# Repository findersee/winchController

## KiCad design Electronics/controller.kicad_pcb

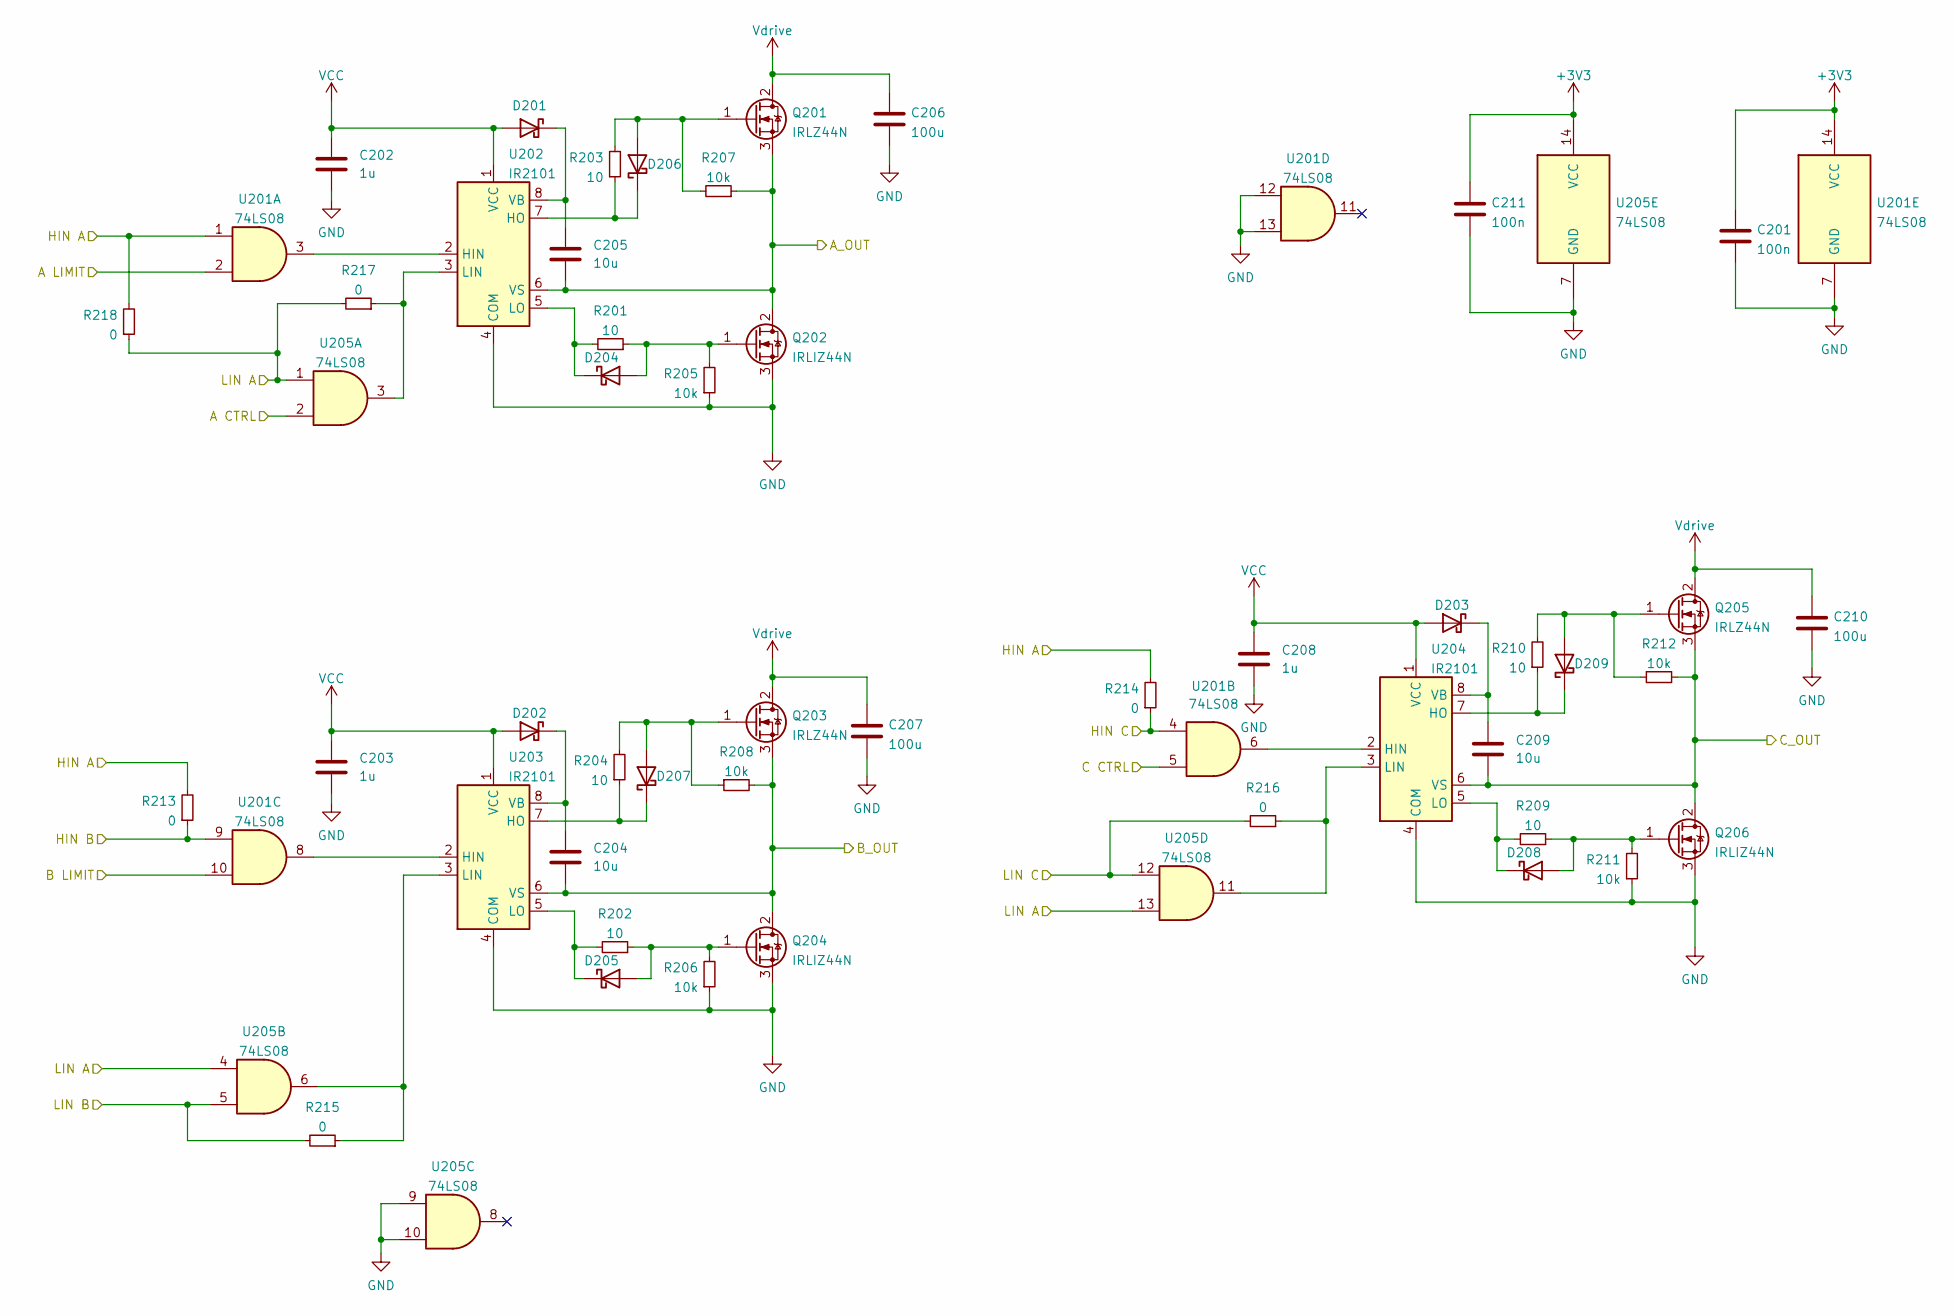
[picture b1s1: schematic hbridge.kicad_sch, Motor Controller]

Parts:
C201, C211: 100n; C_0603_1608Metric_Pad1.08x0.95mm_HandSolder
C202, C203, C208: 1u; C_0603_1608Metric_Pad1.08x0.95mm_HandSolder
C204, C205, C209: 10u; R_0805_2012Metric_Pad1.20x1.40mm_HandSolder
C206, C207, C210: 100u; CP_Radial_D12.5mm_P3.5-5.0mm
D201, D202, D203, D204, D205, D206, D207, D208, D209: 1N5819; D_SOD-123
Q201, Q203, Q205: IRLZ44N; TO-220-3_Vertical
Q202, Q204, Q206: IRLIZ44N; TO-220F-3_Vertical
R201, R202, R203, R204, R209, R210: 10; R_0805_2012Metric_Pad1.20x1.40mm_HandSolder
R205, R206, R207, R208, R211, R212: 10k; R_0805_2012Metric_Pad1.20x1.40mm_HandSolder
R213, R214, R215, R216, R217, R218: 0; R_0603_1608Metric_Pad0.98x0.95mm_HandSolder
U201, U205: 74LS08; SO-14_3.9x8.65mm_P1.27mm
U202, U203, U204: IR2101; SO-8_3.9x4.9mm_P1.27mm

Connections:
+3V3: C201.1, C211.1, U201.14 (VCC), U205.14 (VCC); also elsewhere on the board
/Connectors/Limit 1: U201.2; also elsewhere on the board
/Connectors/Limit 2: U201.10; also elsewhere on the board
/Connectors/MOTOR C: C209.1, Q205.3 (S), Q206.2 (D), R212.2, U204.6 (VS); also elsewhere on the board
/Connectors/MOTOR NEG: C204.1, Q203.3 (S), Q204.2 (D), R208.2, U203.6 (VS); also elsewhere on the board
/Connectors/MOTOR POS: C205.1, Q201.3 (S), Q202.2 (D), R207.1, U202.6 (VS); also elsewhere on the board
/Hbridge/A CTRL: U205.2; also elsewhere on the board
/Hbridge/C CTRL: U201.5; also elsewhere on the board
/Hbridge/HIN A: R213.2, R214.2, R218.2, U201.1; also elsewhere on the board
/Hbridge/HIN B: R213.1, U201.9; also elsewhere on the board
/Hbridge/HIN C: R214.1, U201.4; also elsewhere on the board
/Hbridge/LIN A: R217.2, R218.1, U205.1, U205.4, U205.13; also elsewhere on the board
/Hbridge/LIN B: R215.2, U205.5; also elsewhere on the board
/Hbridge/LIN C: R216.2, U205.12; also elsewhere on the board
GND: C201.2, C202.1, C203.1, C206.2, C207.2, C208.1, C210.2, C211.2, Q202.3 (S), Q204.3 (S), Q206.3 (S), R205.1, R206.1, R211.1, U201.7 (GND), U201.12, U201.13, U202.4 (COM), U203.4 (COM), U204.4 (COM), U205.7 (GND), U205.9, U205.10; also elsewhere on the board
unnamed: C204.2, D202.1 (K), U203.8 (VB)
unnamed: C205.2, D201.1 (K), U202.8 (VB)
unnamed: C209.2, D203.1 (K), U204.8 (VB)
unnamed: D204.1 (K), R201.2, U202.5 (LO)
unnamed: D204.2 (A), Q202.1 (G), R201.1, R205.2
unnamed: D205.1 (K), R202.2, U203.5 (LO)
unnamed: D205.2 (A), Q204.1 (G), R202.1, R206.2
unnamed: D206.1 (K), R203.1, U202.7 (HO)
unnamed: D206.2 (A), Q201.1 (G), R203.2, R207.2
unnamed: D207.1 (K), R204.1, U203.7 (HO)
unnamed: D207.2 (A), Q203.1 (G), R204.2, R208.1
unnamed: D208.1 (K), R209.2, U204.5 (LO)
unnamed: D208.2 (A), Q206.1 (G), R209.1, R211.2
unnamed: D209.1 (K), R210.1, U204.7 (HO)
unnamed: D209.2 (A), Q205.1 (G), R210.2, R212.1
unnamed: R215.1, U203.3 (LIN), U205.6
unnamed: R216.1, U204.3 (LIN), U205.11
unnamed: R217.1, U202.3 (LIN), U205.3
unnamed: U201.3, U202.2 (HIN)
unnamed: U201.6, U204.2 (HIN)
unnamed: U201.8, U203.2 (HIN)
VCC: C202.2, C203.2, C208.2, D201.2 (A), D202.2 (A), D203.2 (A), U202.1 (VCC), U203.1 (VCC), U204.1 (VCC); also elsewhere on the board
Vdrive: C206.1, C207.1, C210.1, Q201.2 (D), Q203.2 (D), Q205.2 (D); also elsewhere on the board

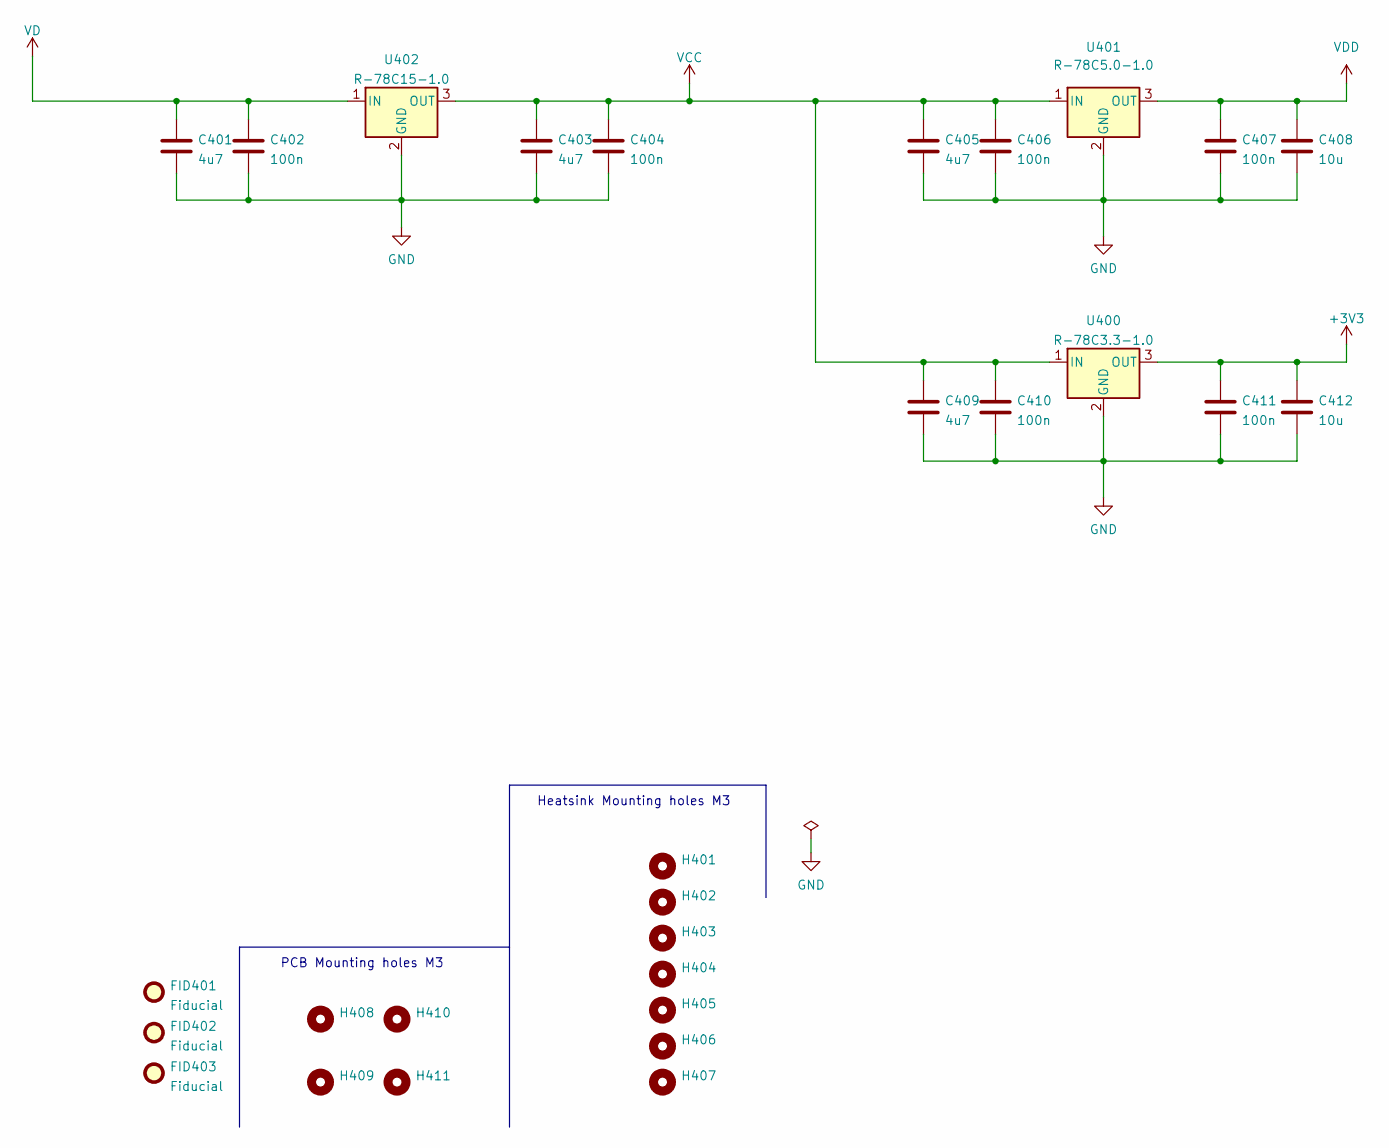
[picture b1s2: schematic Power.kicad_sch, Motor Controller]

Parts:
C401, C403, C405, C409: 4u7; R_0805_2012Metric_Pad1.20x1.40mm_HandSolder
C402, C404, C406, C407, C410, C411: 100n; C_0603_1608Metric_Pad1.08x0.95mm_HandSolder
C408, C412: 10u; R_0805_2012Metric_Pad1.20x1.40mm_HandSolder
FID401, FID402, FID403: Fiducial; Fiducial_1.5mm_Mask3mm
H401, H402, H403, H404, H405, H406, H407, H408, H409, H410, H411: MountingHole; MountingHole_3.2mm_M3_DIN965
U400: R-78C3.3-1.0; Converter_DCDC_RECOM_R-78E-0.5_THT
U401: R-78C5.0-1.0; Converter_DCDC_RECOM_R-78E-0.5_THT
U402: R-78C15-1.0; Converter_DCDC_RECOM_R-78E-0.5_THT

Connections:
+3V3: C411.1, C412.1, U400.3 (OUT); also elsewhere on the board
GND: C401.2, C402.2, C403.2, C404.2, C405.2, C406.2, C407.2, C408.2, C409.2, C410.2, C411.2, C412.2, U400.2 (GND), U401.2 (GND), U402.2 (GND); also elsewhere on the board
VCC: C403.1, C404.1, C405.1, C406.1, C409.1, C410.1, U400.1 (IN), U401.1 (IN), U402.3 (OUT); also elsewhere on the board
VD: C401.1, C402.1, U402.1 (IN); also elsewhere on the board
VDD: C407.1, C408.1, U401.3 (OUT); also elsewhere on the board

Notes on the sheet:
PCB Mounting holes M3
Heatsink Mounting holes M3

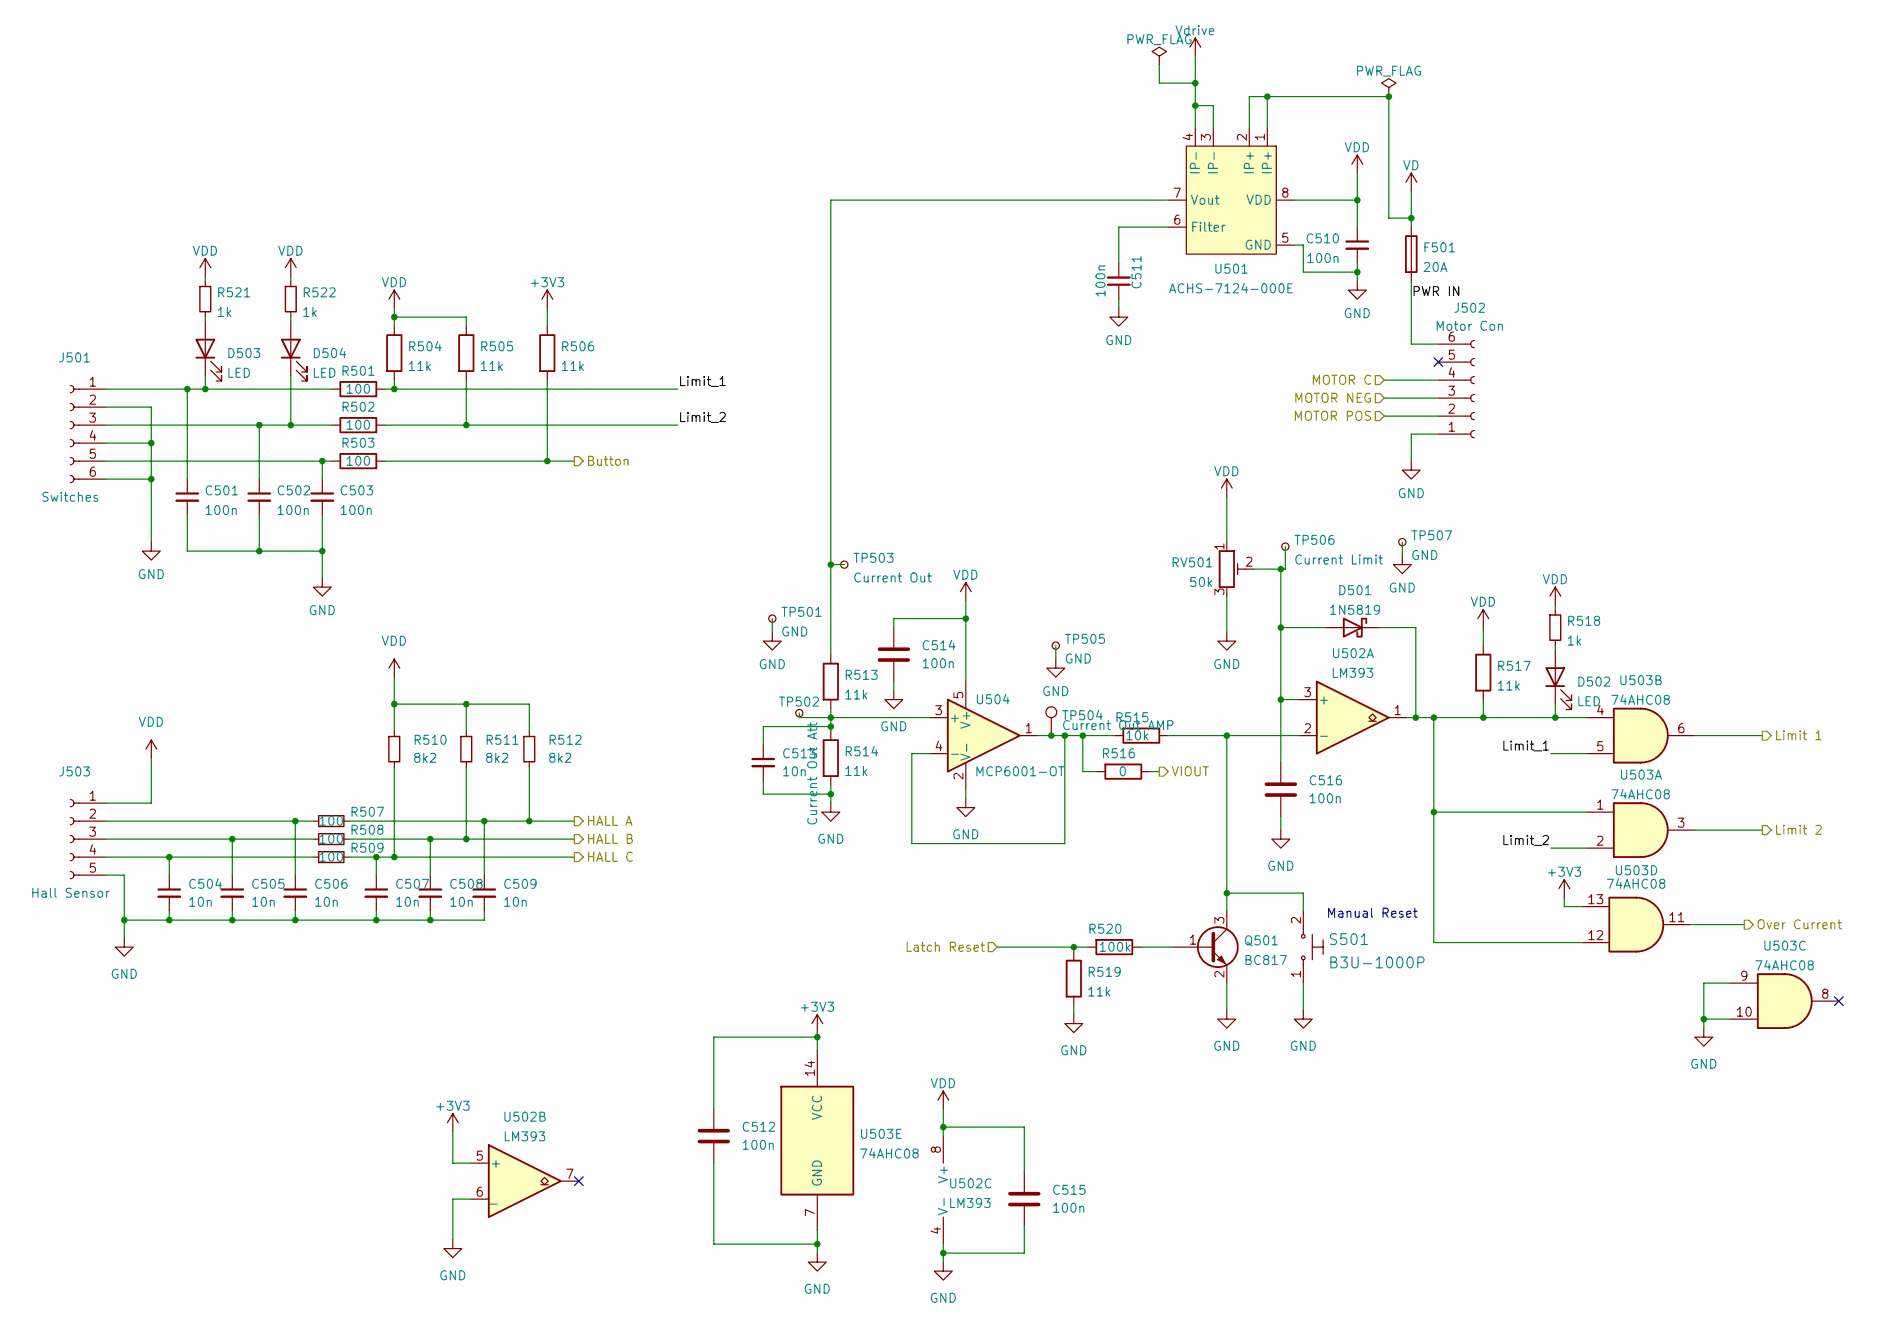
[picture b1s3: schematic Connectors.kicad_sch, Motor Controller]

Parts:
C501, C502, C503, C510, C511, C512, C514, C515, C516: 100n; C_0603_1608Metric_Pad1.08x0.95mm_HandSolder
C504, C505, C506, C507, C508, C509, C513: 10n; C_0603_1608Metric_Pad1.08x0.95mm_HandSolder
D501: 1N5819; D_SOD-123
D502, D503, D504: LED; LED_1206_3216Metric_Pad1.42x1.75mm_HandSolder
F501: 20A; 3550-2_KEYS
J501: Switches; TerminalBlock_bornier-6_P5.08mm
J502: Motor Con; TerminalBlock_bornier-6_P5.08mm
J503: Hall Sensor; PinHeader_1x05_P2.54mm_Vertical
Q501: BC817; SOT-23
R501, R502, R503, R507, R508, R509: 100; R_0603_1608Metric_Pad0.98x0.95mm_HandSolder
R504, R505, R506, R513, R514, R517, R519: 11k; R_0603_1608Metric_Pad0.98x0.95mm_HandSolder
R510, R511, R512: 8k2; R_0603_1608Metric_Pad0.98x0.95mm_HandSolder
R515: 10k; R_0603_1608Metric_Pad0.98x0.95mm_HandSolder
R516: 0; R_0603_1608Metric_Pad0.98x0.95mm_HandSolder
R518, R521, R522: 1k; LED_0603_1608Metric_Pad1.05x0.95mm_HandSolder
R520: 100k; R_0603_1608Metric_Pad0.98x0.95mm_HandSolder
RV501: 50k; Potentiometer_Vishay_TS53YJ_Vertical
S501: B3U-1000P; Switch_Tactile_SMD_B3U-1000P; MPN B3U-1000P; Digi-Key_PN SW1020CT-ND
TP501, TP505, TP507: GND; TestPoint_Pad_1.5x1.5mm
TP502: Current Out Att; TestPoint_Pad_D1.0mm
TP503: Current Out; TestPoint_Pad_D1.0mm
TP504: Current Out AMP; TestPoint_Pad_D1.0mm
TP506: Current Limit; TestPoint_Pad_D1.0mm
U501: ‎ACHS-7124-000E‎; SO-8_3.9x4.9mm_P1.27mm
U502: LM393; SO-8_3.9x4.9mm_P1.27mm
U503: 74AHC08; SSOP-14_5.3x6.2mm_P0.65mm
U504: MCP6001-OT; SOT-23-5

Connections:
+3V3: C512.2, R506.1, U502.5 (+), U503.13, U503.14 (VCC); also elsewhere on the board
/Connectors/Button: R503.2, R506.2; also elsewhere on the board
/Connectors/HALL A: C509.1, R507.2, R512.2; also elsewhere on the board
/Connectors/HALL B: C508.1, R508.2, R511.2; also elsewhere on the board
/Connectors/HALL C: C507.1, R509.2, R510.2; also elsewhere on the board
/Connectors/Latch Reset: R519.1, R520.2; also elsewhere on the board
/Connectors/Limit 1: U503.6; also elsewhere on the board
/Connectors/Limit 2: U503.3; also elsewhere on the board
/Connectors/Limit_1: R501.2, R504.2, U503.5
/Connectors/Limit_2: R502.2, R505.2, U503.2
/Connectors/MOTOR C: J502.4; also elsewhere on the board
/Connectors/MOTOR NEG: J502.3; also elsewhere on the board
/Connectors/MOTOR POS: J502.2; also elsewhere on the board
/Connectors/Over Current: U503.11; also elsewhere on the board
/Connectors/PWR IN: F501.2, J502.6
/Connectors/VIOUT: R516.1; also elsewhere on the board
GND: C501.2, C502.2, C503.2, C504.2, C505.2, C506.2, C507.2, C508.2, C509.2, C510.2, C511.1, C512.1, C513.2, C514.1, C515.1, C516.1, J501.2, J501.4, J501.6, J502.1, J503.5, Q501.2 (E), R514.2, R519.2, RV501.3, S501.1, TP501.1, TP505.1, TP507.1, U501.5 (GND), U502.4 (V-), U502.6 (_), U503.7 (GND), U503.9, U503.10, U504.2 (V-); also elsewhere on the board
unnamed: C501.1, D503.1 (K), J501.1, R501.1
unnamed: C502.1, D504.1 (K), J501.3, R502.1
unnamed: C503.1, J501.5, R503.1
unnamed: C504.1, J503.4, R509.1
unnamed: C505.1, J503.3, R508.1
unnamed: C506.1, J503.2, R507.1
unnamed: C511.2, U501.6 (Filter)
unnamed: C513.1, R513.2, R514.1, TP502.1, U504.3 (+)
unnamed: C516.2, D501.2 (A), RV501.2, TP506.1, U502.3 (+)
unnamed: D501.1 (K), D502.1 (K), R517.2, U502.1, U503.1, U503.4, U503.12
unnamed: D502.2 (A), R518.2
unnamed: D503.2 (A), R521.2
unnamed: D504.2 (A), R522.2
unnamed: Q501.1 (B), R520.1
unnamed: Q501.3 (C), R515.1, S501.2, U502.2 (-)
unnamed: R513.1, TP503.1, U501.7 (Vout)
unnamed: R515.2, R516.2, TP504.1, U504.1, U504.4 (-)
VD: F501.1, U501.1 (IP+), U501.2 (IP+); also elsewhere on the board
VDD: C510.1, C514.2, C515.2, J503.1, R504.1, R505.1, R510.1, R511.1, R512.1, R517.1, R518.1, R521.1, R522.1, RV501.1, U501.8 (VDD), U502.8 (V+), U504.5 (V+); also elsewhere on the board
Vdrive: U501.3 (IP-), U501.4 (IP-); also elsewhere on the board

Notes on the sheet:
Manual Reset

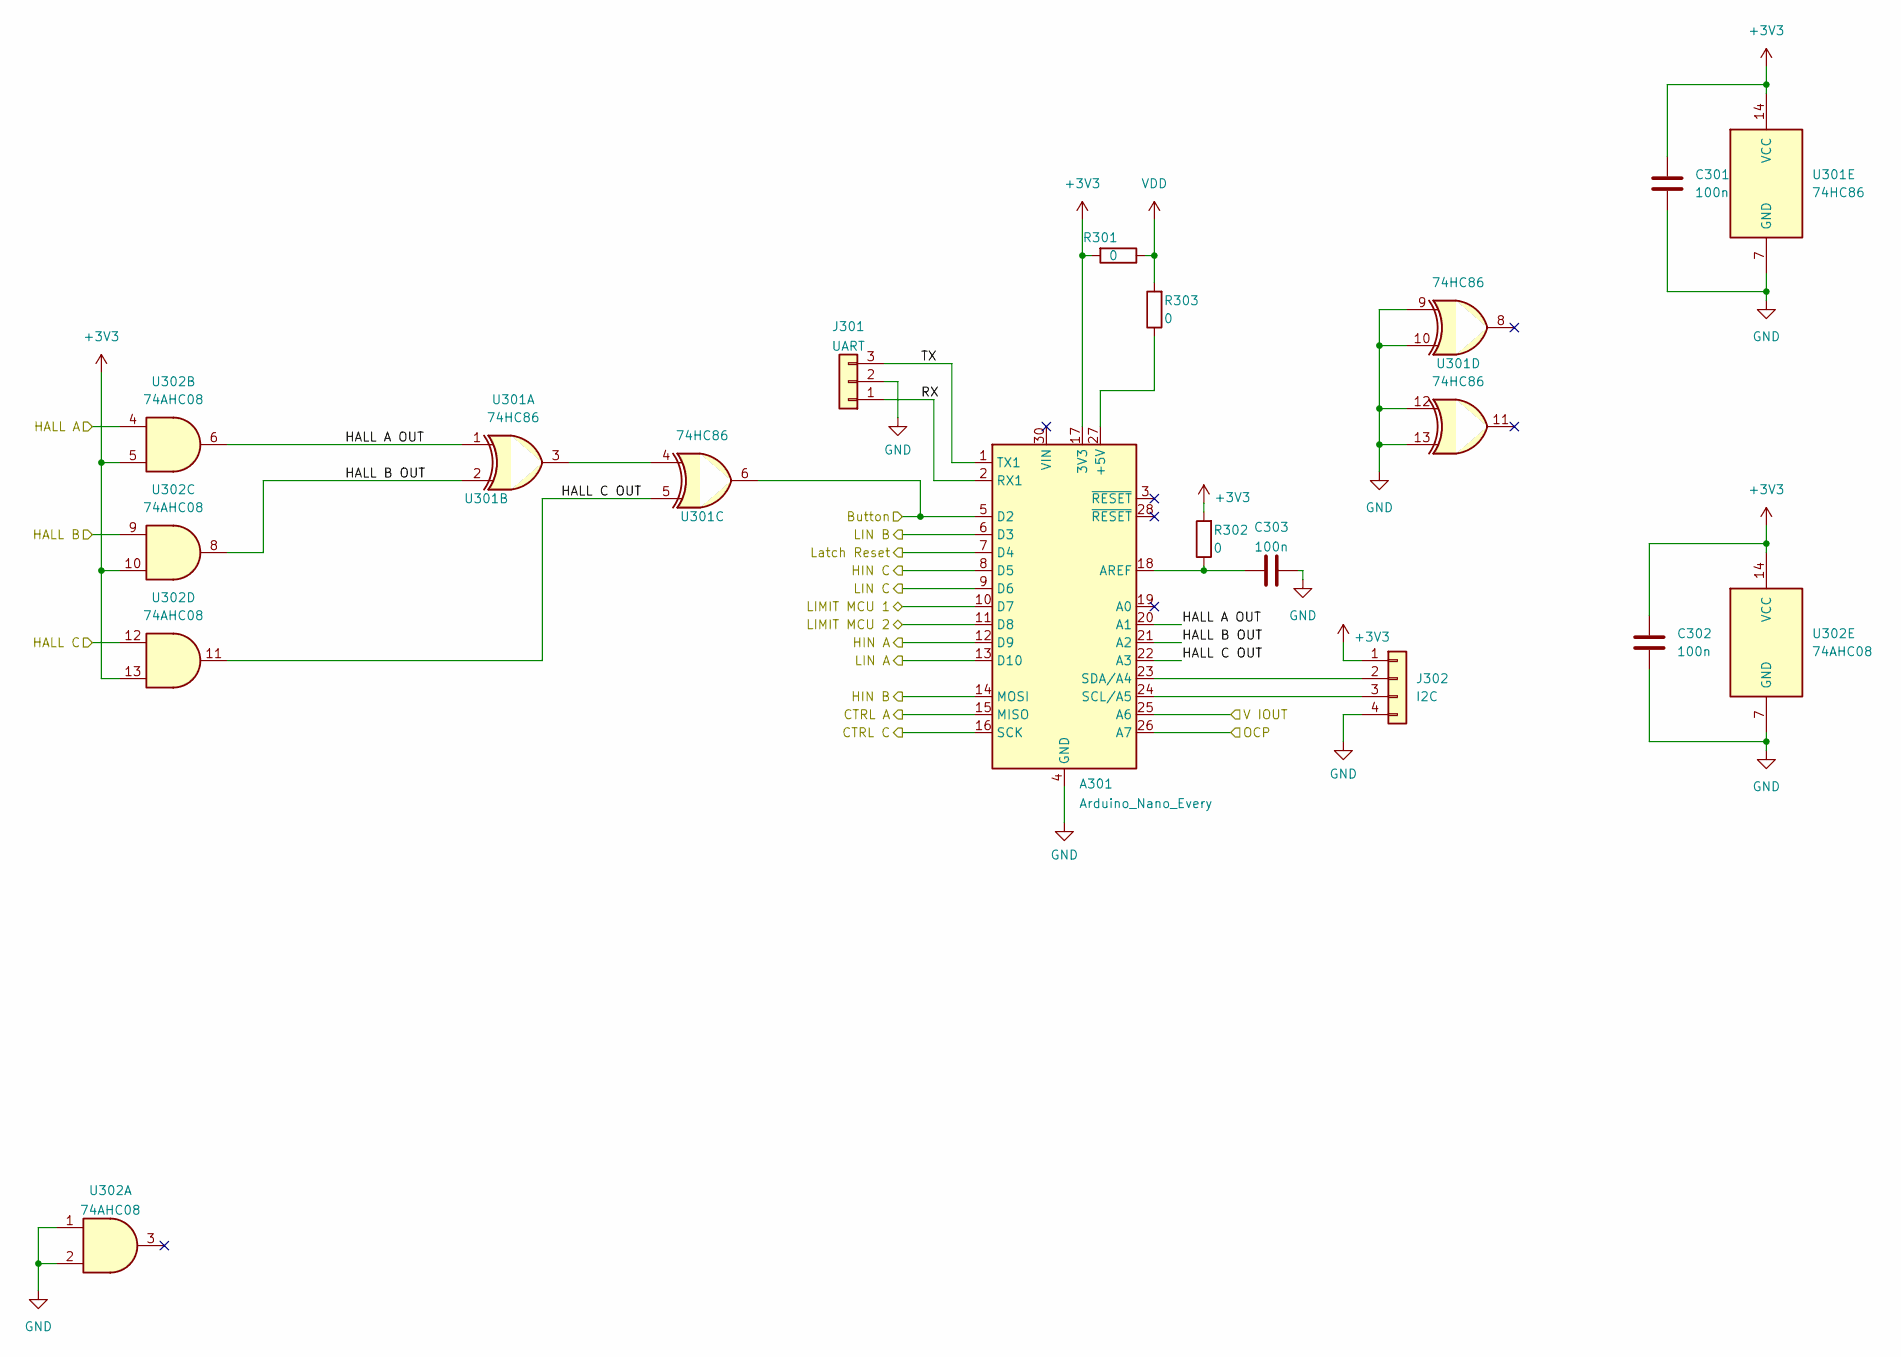
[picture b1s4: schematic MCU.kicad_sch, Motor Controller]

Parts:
A301: Arduino_Nano_Every; Arduino_Nano
C301, C302, C303: 100n; C_0603_1608Metric_Pad1.08x0.95mm_HandSolder
J301: UART; PinHeader_1x03_P2.54mm_Vertical
J302: I2C; PinHeader_1x04_P2.54mm_Vertical
R301, R302, R303: 0; R_0603_1608Metric_Pad0.98x0.95mm_HandSolder
U301: 74HC86; SO-14_3.9x8.65mm_P1.27mm
U302: 74AHC08; SSOP-14_5.3x6.2mm_P0.65mm

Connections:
+3V3: A301.17 (3V3), C301.2, C302.2, J302.1, R301.2, R302.2, U301.14 (VCC), U302.5, U302.10, U302.13, U302.14 (VCC); also elsewhere on the board
/Connectors/Button: A301.5 (D2), U301.6; also elsewhere on the board
/Connectors/HALL A: U302.4; also elsewhere on the board
/Connectors/HALL B: U302.9; also elsewhere on the board
/Connectors/HALL C: U302.12; also elsewhere on the board
/Connectors/Latch Reset: A301.7 (D4); also elsewhere on the board
/Connectors/Limit 1: A301.10 (D7); also elsewhere on the board
/Connectors/Limit 2: A301.11 (D8); also elsewhere on the board
/Connectors/Over Current: A301.26 (A7); also elsewhere on the board
/Connectors/VIOUT: A301.25 (A6); also elsewhere on the board
/Hbridge/A CTRL: A301.15 (MISO); also elsewhere on the board
/Hbridge/C CTRL: A301.16 (SCK); also elsewhere on the board
/Hbridge/HIN A: A301.12 (D9); also elsewhere on the board
/Hbridge/HIN B: A301.14 (MOSI); also elsewhere on the board
/Hbridge/HIN C: A301.8 (D5); also elsewhere on the board
/Hbridge/LIN A: A301.13 (D10); also elsewhere on the board
/Hbridge/LIN B: A301.6 (D3); also elsewhere on the board
/Hbridge/LIN C: A301.9 (D6); also elsewhere on the board
/MCU/HALL A OUT: A301.20 (A1), U301.1, U302.6
/MCU/HALL B OUT: A301.21 (A2), U301.2, U302.8
/MCU/HALL C OUT: A301.22 (A3), U301.5, U302.11
/MCU/RX: A301.2 (RX1), J301.1
/MCU/TX: A301.1 (TX1), J301.3
GND: A301.4 (GND), A301.29 (GND), C301.1, C302.1, C303.1, J301.2, J302.4, U301.7 (GND), U301.9, U301.10, U301.12, U301.13, U302.1, U302.2, U302.7 (GND); also elsewhere on the board
unnamed: A301.18 (AREF), C303.2, R302.1
unnamed: A301.23 (SDA/A4), J302.2
unnamed: A301.24 (SCL/A5), J302.3
unnamed: A301.27 (+5V), R303.1
unnamed: U301.3, U301.4
VDD: R301.1, R303.2; also elsewhere on the board

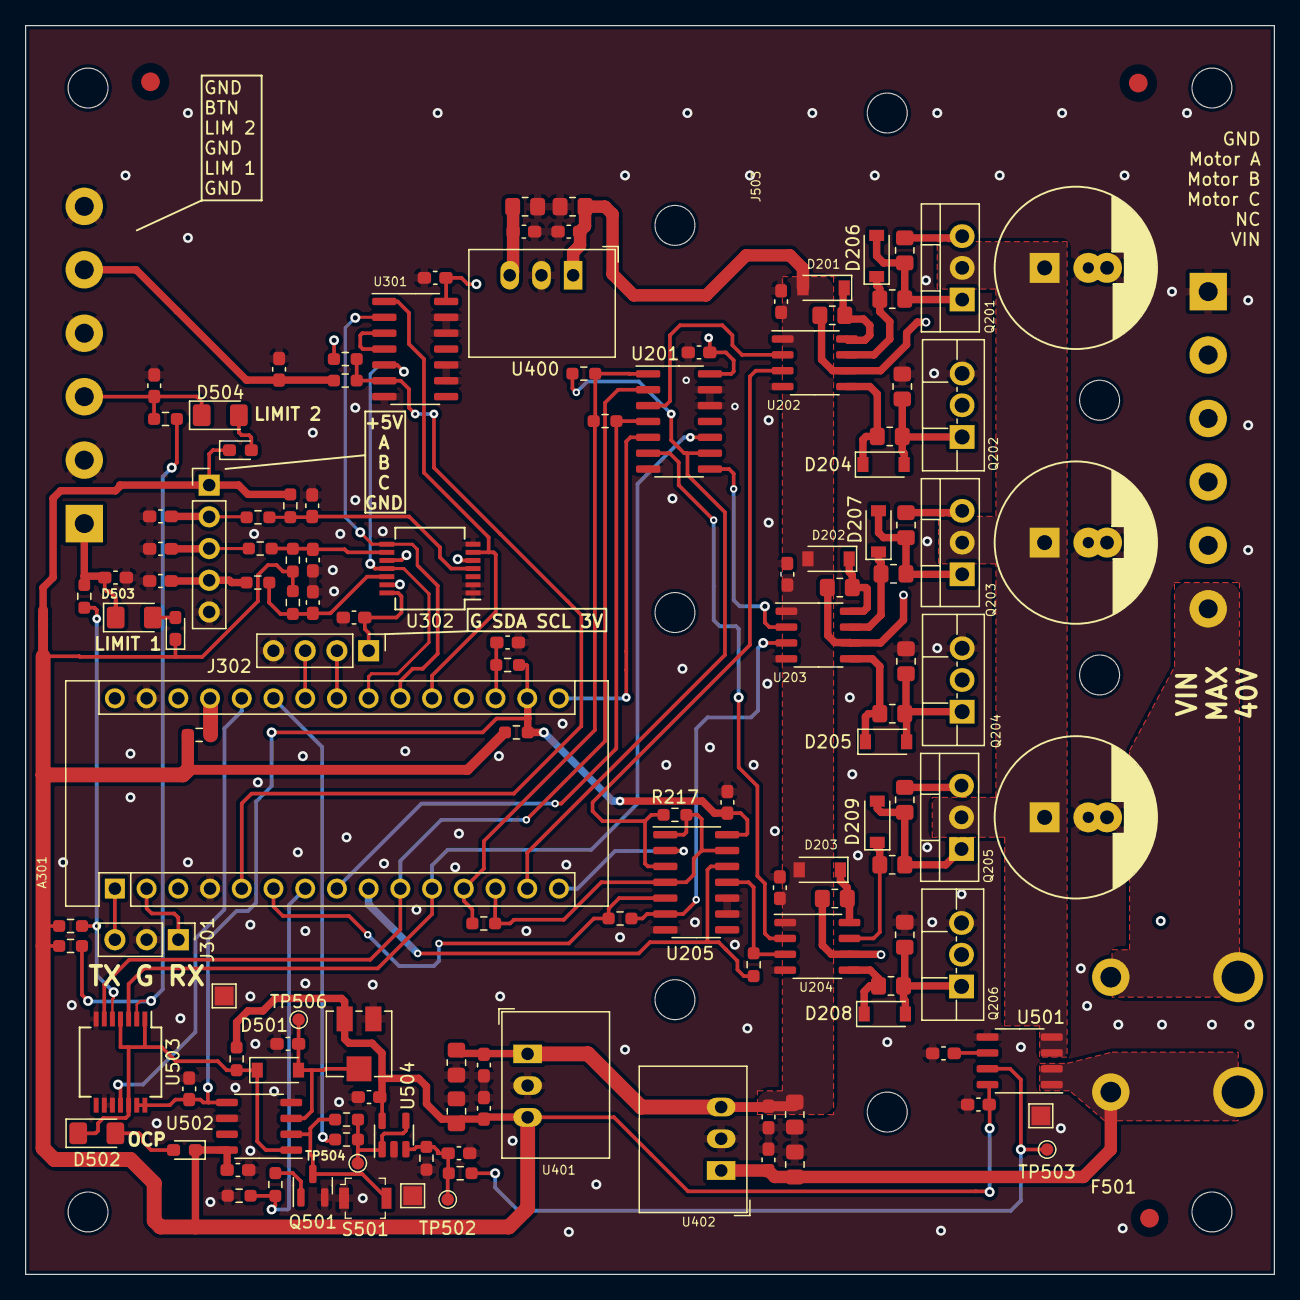
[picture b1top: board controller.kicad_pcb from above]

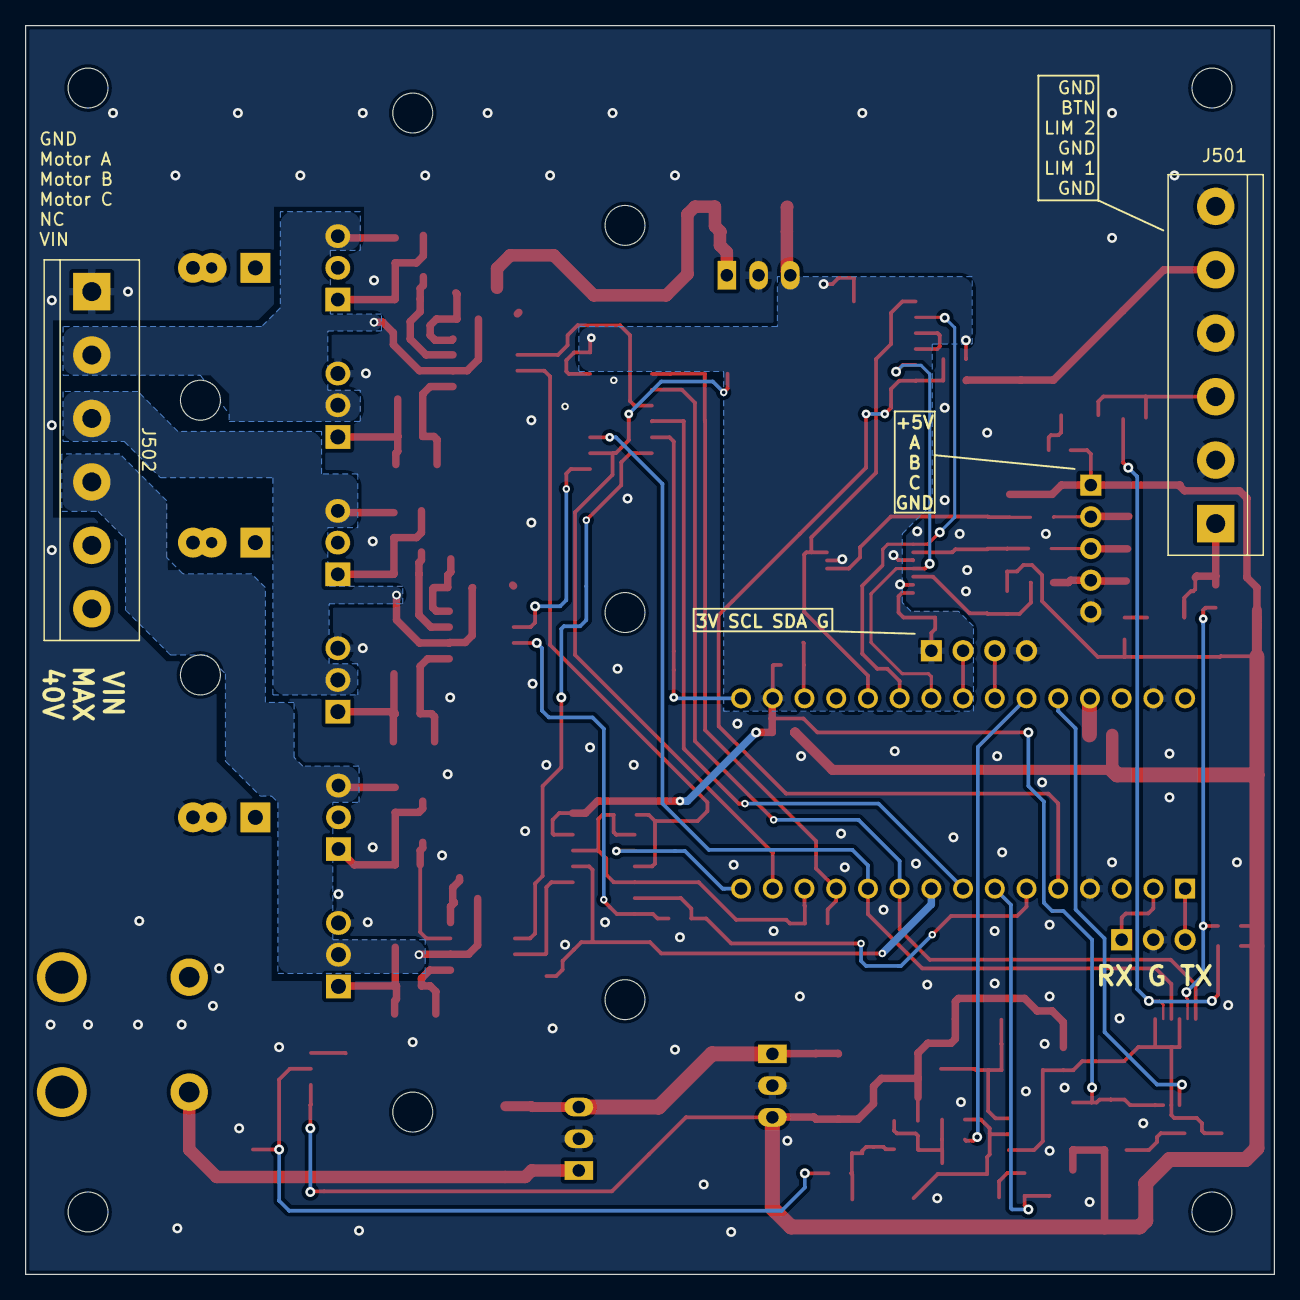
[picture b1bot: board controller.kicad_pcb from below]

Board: 2 copper layers, 100.0 x 100.0 mm, 149 parts (2 on the bottom side), 77 nets.

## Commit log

2022-01-25 Added code and Kicad template
2022-01-25 Updated code and pcb
2022-02-10 Hbridge addition
2022-02-11 Added third half bridge for BLDC applications
2022-02-12 Layout update
2022-02-13 Added hall sensor circuitry
2022-02-13 Added Current sensor finalized layout version 0.1
2022-02-14 Added current sensor circuitry
2022-02-17 Updated Design
2022-02-18 Chaned 74AHC08 footprint to ssop-14
2022-02-18 Layout improvements
2022-02-19 Changed capacitor to multi footprint version. Added parallel diodes to MOSFET gate resistors to improve Turn-OFF time.
2022-02-20 Manufacturing commit of PCB
2022-03-30 Added STM32 Code for BLDC controller
